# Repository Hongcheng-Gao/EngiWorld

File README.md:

[English](README.md) | [简体中文](README_CN.md)

<h1 align="center">EngiWorld</h1>
<p align="center"><strong>What Can Frontier Agents Deliver in Professional Engineering Environments?</strong></p>

<p align="center">
  <a href="https://engiworld.github.io/">🌐 Website</a> ·
  <a href="https://arxiv.org/abs/2609.37686">📄 Paper</a> ·
  <a href="task/">🧩 Tasks &amp; Verifiers</a> ·
  <a href="https://huggingface.co/datasets/HongchengGao/EngiWorld-Tasks">🤗 Task Dataset</a> ·
  <a href="https://huggingface.co/datasets/HongchengGao/EngiWorld-Images">🤗 Environment Images</a>
</p>

<p align="center"></p>

<p align="center"></p>

<p align="center"><em>Six task types for engineering software use and artifact-based evaluation. Click to enlarge.</em></p>

EngiWorld evaluates whether agents can operate professional engineering software and deliver the requested engineering artifacts. This repository provides all **1,301 tasks**, their evaluators, and the GUI/CLI evaluation runtime. The paper uses a 306-task main-experiment subset, listed in [`task/splits/main-306.txt`](task/splits/main-306.txt).

The full set of 1,301 tasks and their verifiers is also available in the [Hugging Face task dataset](https://huggingface.co/datasets/HongchengGao/EngiWorld-Tasks), with a [dataset viewer](https://huggingface.co/datasets/HongchengGao/EngiWorld-Tasks/viewer/default/tasks) for browsing task instructions and metadata.

The benchmark covers CAD, CAE, CAM, BIM, EDA, and DCC. Its six task types are Single-Software Execution (931), Software Selection (140), Vision-Guided Modeling (120), Design Optimization (40), Cross-Software Coordination (60), and Open-Environment Engineering (10).

Local evaluation launches Windows or Ubuntu virtual machines through Docker on Linux, calls the model, and saves evaluation results.

## ☁️ Run on Alibaba Cloud or Volcengine

Use the [cloud evaluation guide](runtime/deploy/cloud/README.md) for single-task or
Redis-scheduled batch evaluation on either cloud. Explicit model presets, API
interruption handling and batch state management are shared. Images require
compatible engineering applications and desktop services.

## 💾 Installation

Prepare an x86_64 Linux server with Python 3.10, [Docker Engine](https://docs.docker.com/engine/install/), and `zstd`. With `/dev/kvm`, the VM uses hardware acceleration. Without it, the Docker runner attempts software emulation, which starts and runs more slowly. Each environment defaults to 4 CPUs and 16 GB RAM.

Get the code and enter the runtime directory:

```bash
git clone --branch main --single-branch --depth 1 https://github.com/Hongcheng-Gao/Engiworld.git &&
cd Engiworld/runtime
```

Install the runtime in a Python `venv` environment:

```bash
python3.10 -m venv .venv
source .venv/bin/activate
python -m pip install -e ".[worker-api,download]"
```

Run the following commands from `runtime/`.

## 💾 Download complete data before evaluation

The complete dataset provides all **1,301 task definitions, drawings, evaluators, and required ground-truth files**. GitHub includes every drawing and evaluator plus smaller task resources. Download the complete data before starting evaluation.

| Source | Complete task data | Environment images |
|---|---|---|
| Hugging Face | [EngiWorld-Tasks](https://huggingface.co/datasets/HongchengGao/EngiWorld-Tasks) | [EngiWorld-Images](https://huggingface.co/datasets/HongchengGao/EngiWorld-Images) |
| ModelScope | [EngiWorld-Tasks](https://modelscope.cn/datasets/HongchengGao/EngiWorld-Tasks) | [EngiWorld-Images](https://modelscope.cn/datasets/HongchengGao/EngiWorld-Images) |

Use `--source modelscope` in the commands below to download from ModelScope.

**Hugging Face:**

```bash
python -m engiworld.prepare_tasks --source hf --task-root ../data/task
python -m engiworld.prepare_images --source hf --image LibreCAD2.2.0.2 --image-root ../environment-images
```

**ModelScope:**

```bash
python -m engiworld.prepare_tasks --source modelscope --task-root ../data/task
python -m engiworld.prepare_images --source modelscope --image LibreCAD2.2.0.2 --image-root ../environment-images
```

```bash
zstd -d ../environment-images/images/LibreCAD2.2.0.2.qcow2.zst
docker pull happysixd/osworld-docker
python -m engiworld.prepare_tasks --task-root ../data/task --check
```

Downloads verify checksums and preserve modified local files. ModelScope image downloads use 8 parallel range streams by default; set `MODELSCOPE_DOWNLOAD_PARALLEL_WORKERS` to adjust this. Omitting --image downloads all 15 public archives (about 98 GB compressed). Choose the image matching the task snapshot from manifest.json. Snapshots outside the public catalog require a matching image prepared by the user. Decompress the selected archive and prepare the Docker runner before evaluation. Task preparation uses the published dataset directly.

## 🚀 Start from local data

The following commands read already downloaded task data and the local image.

### 1. Start a task

```bash
python -m engiworld.local_eval \
  --task-root ../data/task \
  --task single-software-execution/gui/librecad/task-08 \
  --image ../environment-images/images/LibreCAD2.2.0.2.qcow2 \
  --smoke-test
```

This starts the VM, loads the task inputs, and saves a `smoke.png` screenshot in the results directory without calling a model.

**Servers without KVM:** Check whether the server provides `/dev/kvm`:

```bash
test -e /dev/kvm && echo "KVM available" || echo "Software emulation"
```

If the output says `Software emulation`, run the same `--smoke-test` command above. The runtime selects software emulation automatically; no arguments need to change. Startup may take several minutes. When the terminal shows `"status": "environment_ready"` and `smoke.png` appears in the results directory, open the screenshot to confirm that LibreCAD and the input drawing are ready. Then follow step 2 to run and score a model.

### 2. Run a model and score the task

Configure an OpenAI-compatible Chat Completions endpoint and run the task:

```bash
export OPENAI_BASE_URL="https://your-api-endpoint/v1"
export OPENAI_API_KEY="your-api-key"

python -m engiworld.local_eval \
  --task-root ../data/task \
  --task single-software-execution/gui/librecad/task-08 \
  --image ../environment-images/images/LibreCAD2.2.0.2.qcow2 \
  --model your-model-name \
  --result-dir results
```

When the run finishes, summary.json summarizes the run, result.txt holds the score, and traj.jsonl records model actions. For another task, change --task and use its matching local image. Complete-data preparation already supplies its resources. See the [runtime guide](runtime/README.md) for more options.

## Repository layout

```text
task/<category>/<gui|cli>/<software or software1--software2>/<task-number>/
runtime/
```

Task categories are `single-software-execution`, `cross-software-coordination`, `software-selection`,
`design-optimization`, `vision-guided-modeling`, and `open-environment-engineering`.
Open-Environment Engineering tasks use **CLI** in a blank environment and live under
`task/open-environment-engineering/cli/agent-selected/`; the agent chooses and installs its tools.

Task JSON IDs follow `<category>--<gui|cli>--<software>--<task-number>--<os>`, for example
`single-software-execution--gui--librecad--task-08--ubuntu`. Use either this ID or its task
directory path with `--task`. See the [task guide](task/README.md).

Directory categories and JSON IDs follow the updated paper taxonomy as of 2026-10-09. `task/aliases.json` preserves historical JSON IDs and directory names; the runtime continues to accept them for task selection. See the full [ID migration map](task/id-migration-20261009.json) and [task taxonomy](task/taxonomy.json).

## 📊 Evaluation results

The main experiment evaluates seven models on the same **306 tasks**: **158 CLI** and **148 GUI**, including all 10 Open-Environment Engineering tasks. EngiScore is the mean task score on a 0–100 scale. Execution metrics average all 306 tasks, including unsuccessful runs; output tokens are reported per turn, in thousands.

| Model | EngiScore | CLI | GUI | Turns/task | Tokens (K/turn) | Cost ($/task) |
| --- | ---: | ---: | ---: | ---: | ---: | ---: |
| Claude Opus 5 | **44.7** | 48.6 | 40.5 | 69.5 | 2.4 | 18.78 |
| GPT-5.6 Sol | 38.6 | 47.9 | 28.6 | 54.2 | 1.0 | 9.57 |
| Qwen3.8 Max | 26.3 | 35.3 | 16.6 | 107.3 | 2.7 | 6.44 |
| Gemini 3.7 Flash | 26.1 | 37.2 | 14.2 | 110.0 | 0.7 | 2.08 |
| DeepSeek V4.1 Flash | 25.9 | 48.3 | 2.0 | 115.3 | 9.8 | 0.80 |
| Kimi K3 | 24.3 | 31.3 | 16.7 | 92.1 | 0.9 | 5.85 |
| Qwen3.8 Flash | 16.7 | 31.5 | 1.0 | 119.6 | 1.3 | 0.44 |

## 📚 Citation

If you use EngiWorld in your research, please cite:

```bibtex
@misc{engiworld2026,
  title = {EngiWorld: What Can Frontier Agents Deliver in Professional Engineering Environments?},
  author = {Hongcheng Gao and Hailong Qu and Yu Lei and Henghui Sun and Haoyang Li and Yipeng Wei and Naihao Xue and Xiaohan Yu and Zhuo Tao and Yihe Zang and Yajiao Wang and Jingyi Tang and Yi Li and Jingjing Zhou and Jie Luo and Bohan Zeng and Chengyu Shen and Hao Jiang and Chong Chen and Bowen Qu and Olive Huang and Zeqiang Wang},
  year = {2026},
  eprint = {2609.37686},
  archivePrefix = {arXiv},
  primaryClass = {cs.AI},
  url = {https://arxiv.org/abs/2609.37686}
}
```

## 📄 License

EngiWorld's original code is released under the [MIT License](LICENSE). See [Third-party notices](THIRD_PARTY_NOTICES.md) for component licenses.

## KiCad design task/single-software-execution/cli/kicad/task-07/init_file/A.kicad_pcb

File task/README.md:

[English](README.md) | [简体中文](README_CN.md)

# EngiWorld tasks

The 1,301 tasks use a common directory layout:

```text
<category>/<gui|cli>/<software or software1--software2>/<task-number>/
```

| Directory category | Paper task type | Full tasks |
|---|---|---:|
| `single-software-execution` | Single-Software Execution | 931 |
| `software-selection` | Software Selection | 140 |
| `vision-guided-modeling` | Vision-Guided Modeling | 120 |
| `design-optimization` | Design Optimization | 40 |
| `cross-software-coordination` | Cross-Software Coordination | 60 |
| `open-environment-engineering` | Open-Environment Engineering | 10 |

Software names are lowercase, without version numbers. Multiple names are joined
with `--`. Open-Environment Engineering tasks use `cli/agent-selected/`. Interface folders contain
only the modes available in that category.

Each task contains a `task-*.json` definition, `init_file/` inputs, and its evaluator
(`eval.py`, with `ground_truth/` where required). IDs use
`<category>--<gui|cli>--<software>--<task-number>--<os>`; operating systems retain
`ubuntu` or `windows` from the task. Reverse-modeling tasks retain a `-reverse`
suffix on the task number to distinguish them from same-numbered tasks.

From `../runtime/`, run `python -m engiworld.prepare_tasks --source hf --task-root ../data/task` to download task resources.
Use either a task directory or its JSON ID with `python -m engiworld.local_eval --task-root ../data/task --task`.
Follow the [quick start](../README.md) to run an evaluation.

The paper's 306-task main-experiment subset is listed in [`splits/main-306.txt`](splits/main-306.txt). The scheduler accepts it through `--task-id-file ../task/splits/main-306.txt`.

Directory categories and JSON IDs follow the updated paper taxonomy as of 2026-10-09. `task/aliases.json` preserves historical JSON IDs and directory names; the runtime continues to accept them for task selection. See the full [ID migration map](id-migration-20261009.json) and [task taxonomy](taxonomy.json).

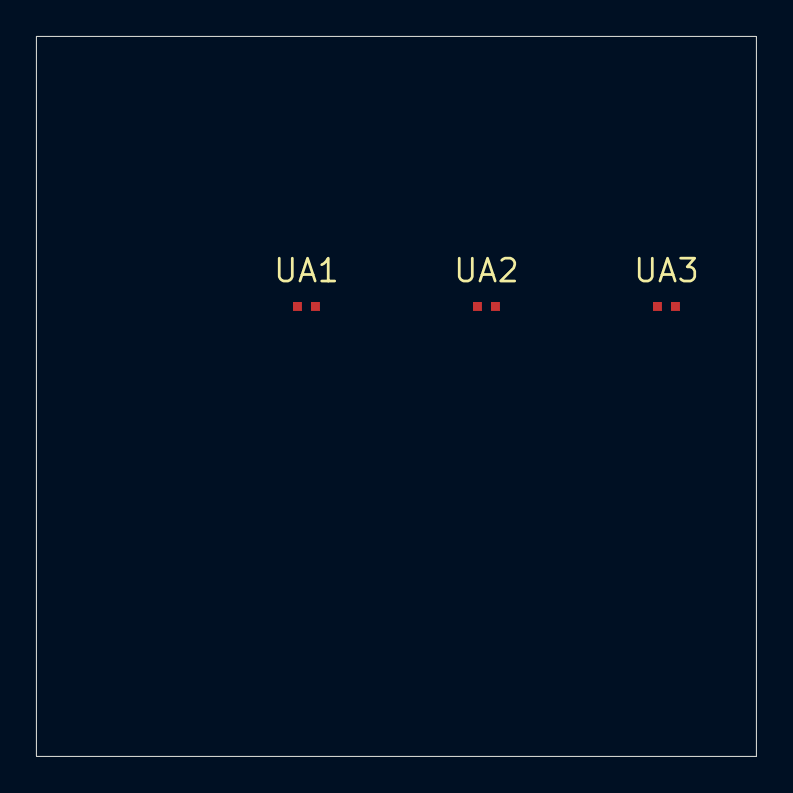
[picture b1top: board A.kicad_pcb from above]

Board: 2 copper layers, 40.0 x 40.0 mm, 3 parts (0 on the bottom side), 2 nets, no tracks yet.

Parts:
UA1: 10k; R_0402_1005Metric
UA2: 22k; R_0402_1005Metric
UA3: 100nF; C_0402_1005Metric

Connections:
GND: UA1.2, UA2.2, UA3.2
VCC: UA1.1, UA2.1, UA3.1

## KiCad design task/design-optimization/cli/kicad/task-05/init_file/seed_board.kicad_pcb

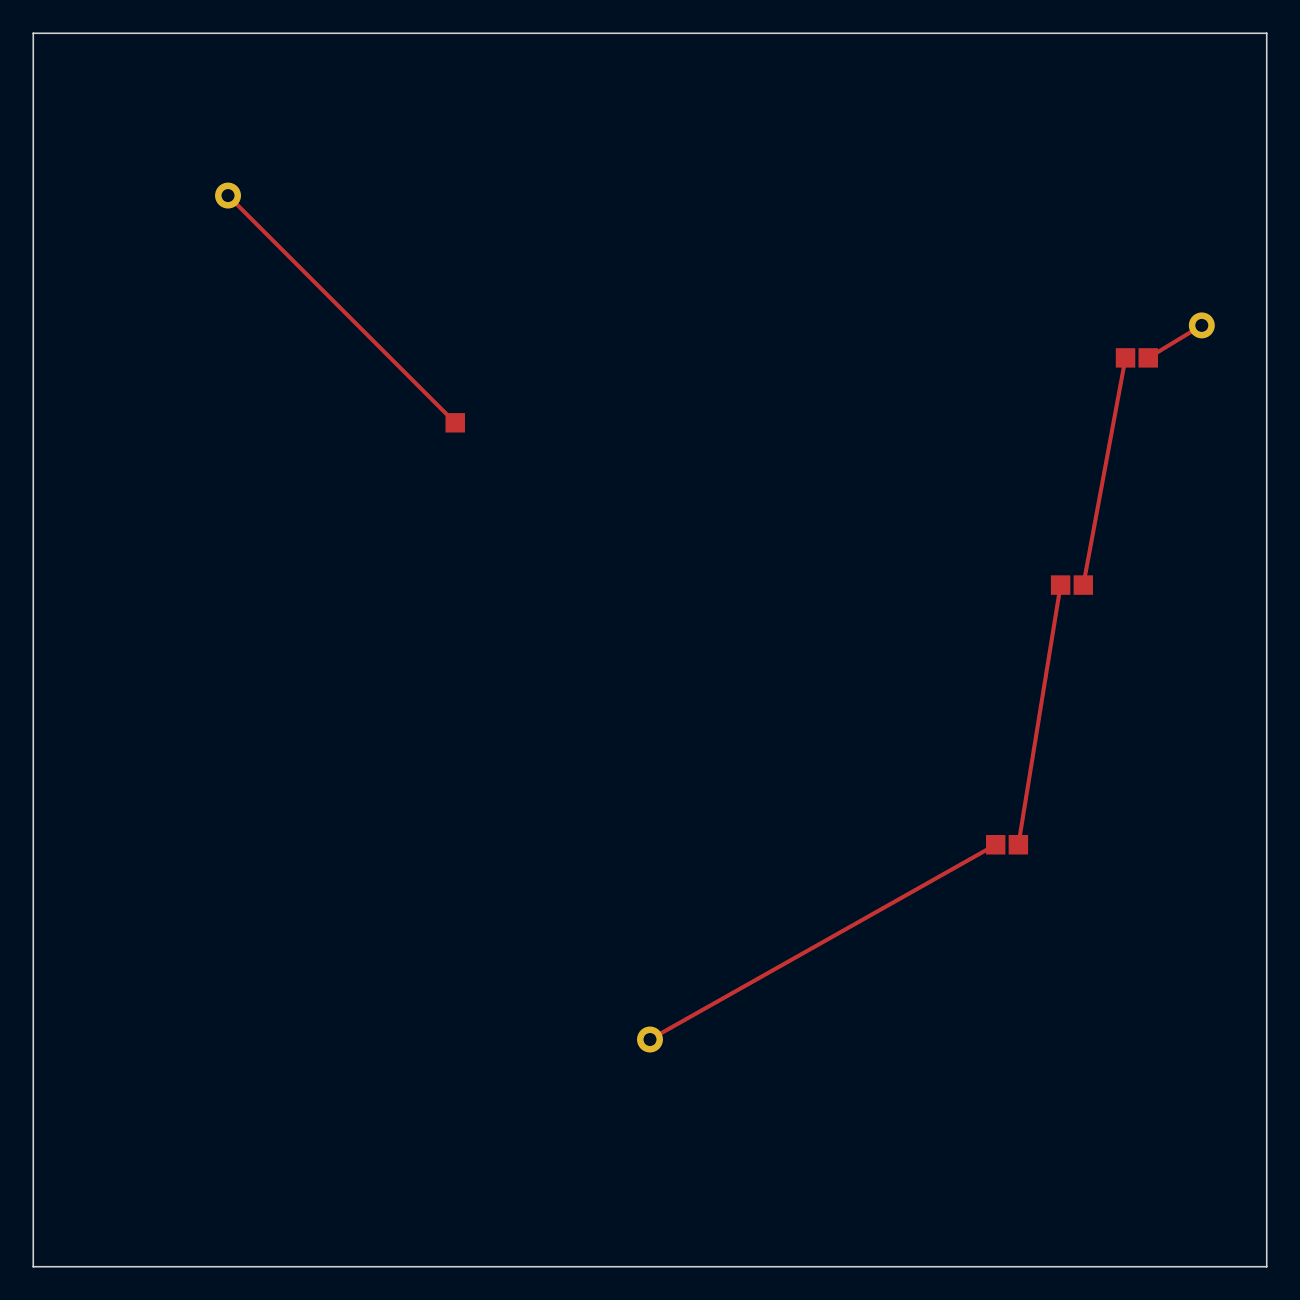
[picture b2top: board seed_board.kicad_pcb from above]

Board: 2 copper layers, 76.0 x 76.0 mm, 7 parts (0 on the bottom side), 5 nets.

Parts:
A1: A1
C1: C1
C2: C2
J1: J1
L1: L1
TP1: TP1
U1: U1

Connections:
A1_C1: A1.1, C1.1
C1_C2: C1.2, C2.1
C2_L1: C2.2, L1.1
L1_J1: J1.1, L1.2
U1_TP1: TP1.1, U1.1

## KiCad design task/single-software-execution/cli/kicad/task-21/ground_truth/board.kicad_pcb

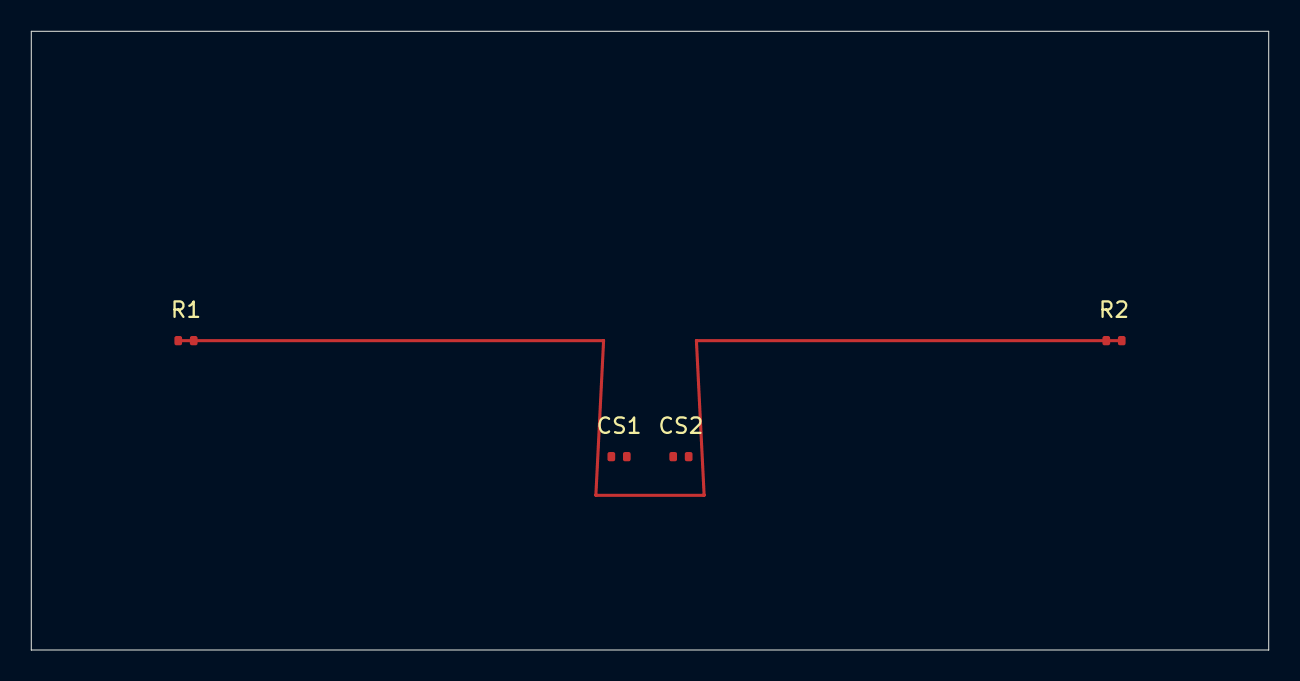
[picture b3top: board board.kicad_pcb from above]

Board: 4 copper layers, 80.0 x 40.0 mm, 4 parts (0 on the bottom side), 3 nets.

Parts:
CS1, CS2: 100n; C_0402
R1, R2: 100; R_0402

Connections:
+3V3: CS1.2, CS2.2
GND: CS1.1, CS2.1
HS1: R1.1, R1.2, R2.1, R2.2

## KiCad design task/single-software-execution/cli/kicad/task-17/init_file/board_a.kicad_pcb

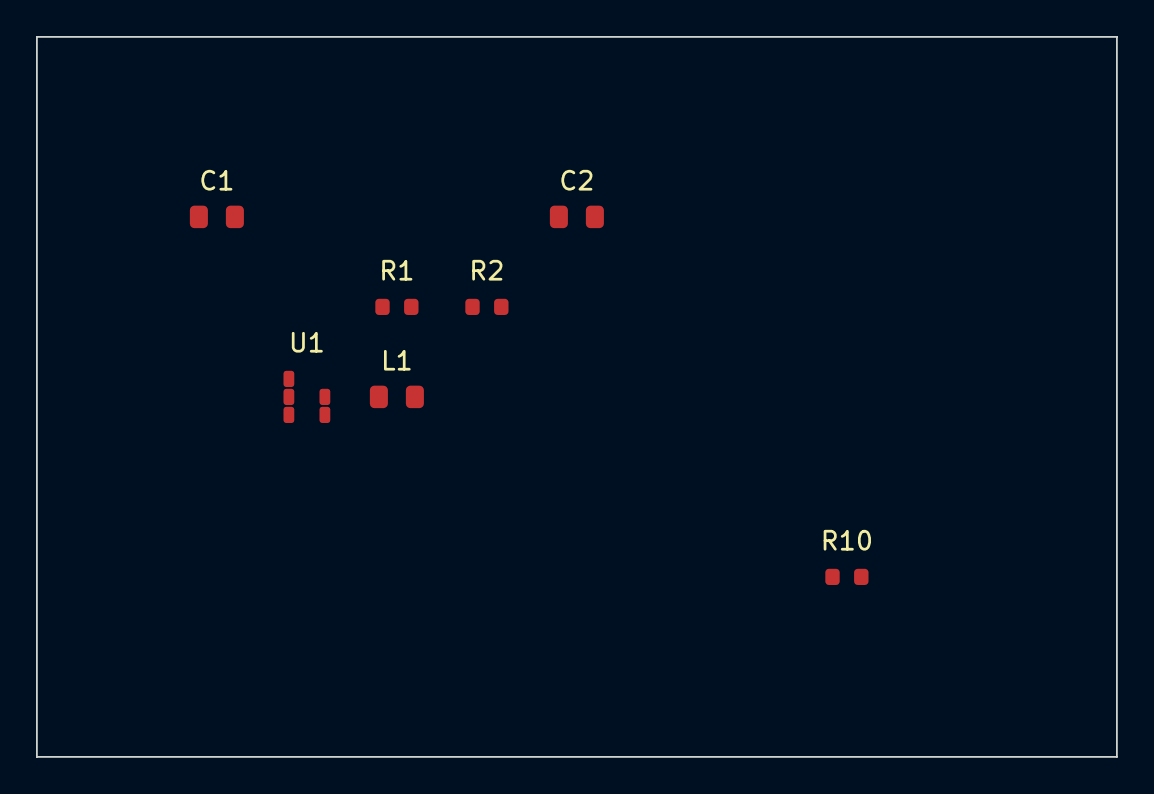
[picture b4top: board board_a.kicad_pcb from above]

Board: 2 copper layers, 60.0 x 40.0 mm, 7 parts (0 on the bottom side), 5 nets, no tracks yet.

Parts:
C1: 10uF; C_0805
C2: 22uF; C_0805
L1: 4u7; L_0805
R1: 10k; R_0603
R2: 2k2; R_0603
R10: 1k; R_0603
U1: LM3671; SOT-23-5

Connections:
FB: R1.2, R2.1, U1.4
GND: C1.2, C2.2, R2.2, R10.2, U1.2
SW: L1.1, U1.1
VIN: C1.1, U1.3, U1.5
VOUT: C2.1, L1.2, R1.1, R10.1

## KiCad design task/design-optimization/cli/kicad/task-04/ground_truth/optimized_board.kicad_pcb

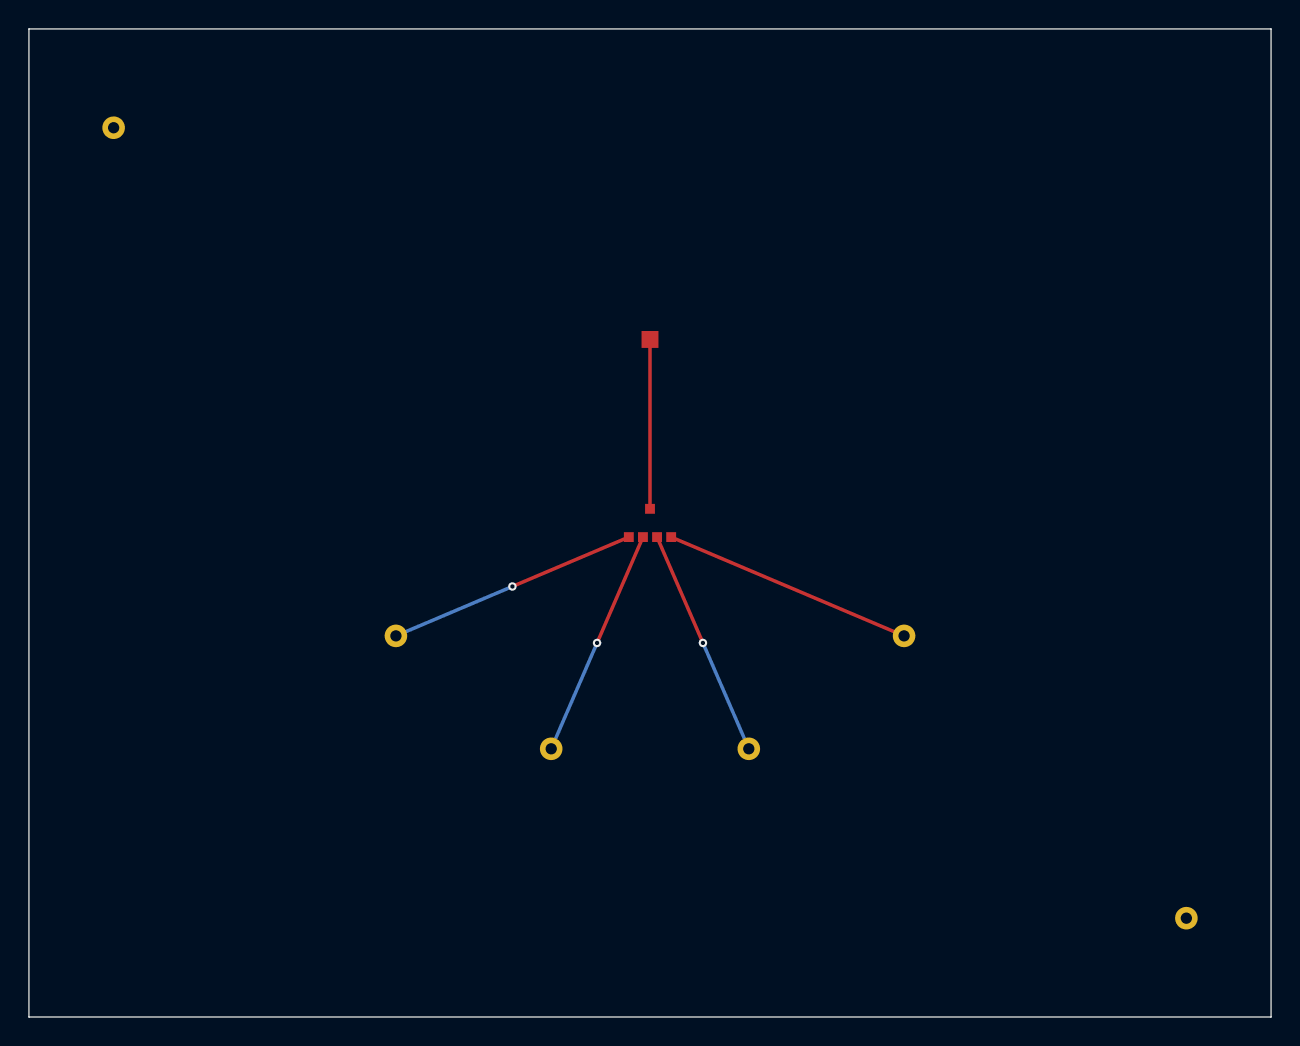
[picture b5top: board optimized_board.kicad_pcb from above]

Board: 2 copper layers, 88.0 x 70.0 mm, 8 parts (0 on the bottom side), 5 nets.

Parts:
C1: C1
J1: J1
J2: J2
TP1, TP2, TP3, TP4: POGO_TEST
U1: U1

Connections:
C1_U1: C1.1, U1.5
TP1_U1: TP1.1, U1.1
TP2_U1: TP2.1, U1.2
TP3_U1: TP3.1, U1.3
TP4_U1: TP4.1, U1.4

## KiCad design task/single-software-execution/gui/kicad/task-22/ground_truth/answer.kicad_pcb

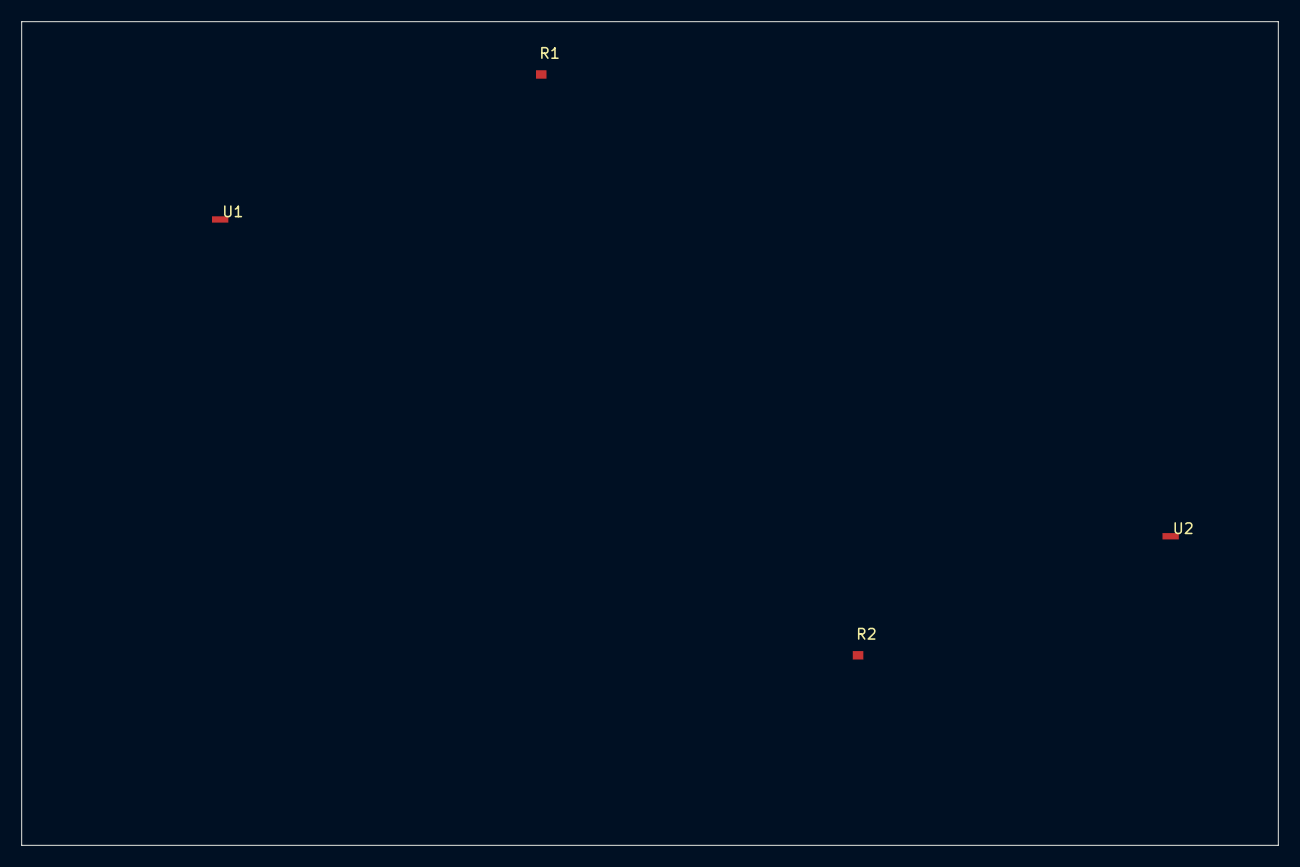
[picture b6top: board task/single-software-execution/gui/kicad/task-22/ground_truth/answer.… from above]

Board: 2 copper layers, 119.0 x 78.0 mm, 4 parts (0 on the bottom side), 2 nets, no tracks yet.

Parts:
R1: 4.7k; R_0603_1608Metric
R2: 10k; R_0603_1608Metric
U1: OPAMP; SOIC-8_3.9x4.9mm_P1.27mm
U2: ADC; SOIC-8_3.9x4.9mm_P1.27mm

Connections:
GND: R2.1, U2.1
VCC: R1.1, U1.1

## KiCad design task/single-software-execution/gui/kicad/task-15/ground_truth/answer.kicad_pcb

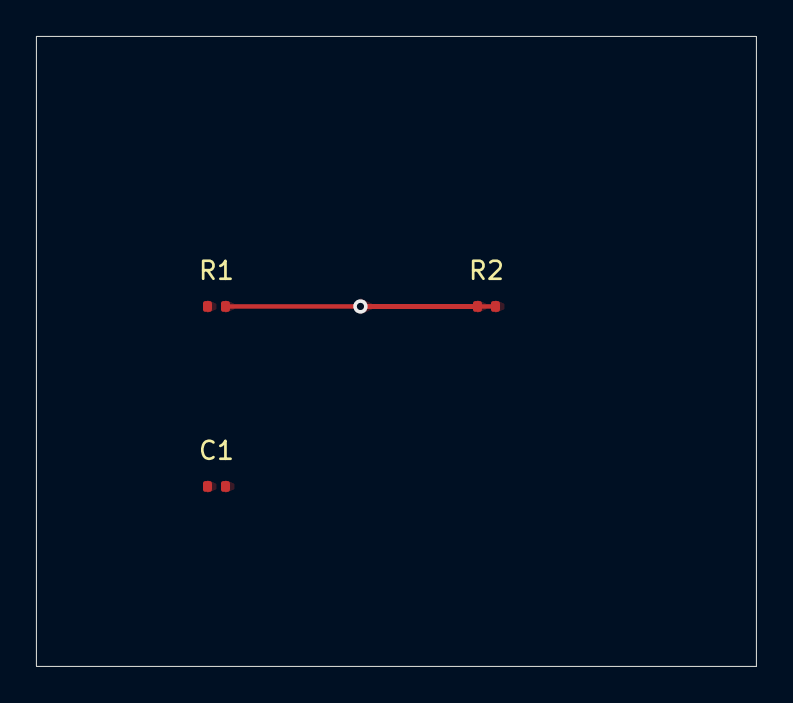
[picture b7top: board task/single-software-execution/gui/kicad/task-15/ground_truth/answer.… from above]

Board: 2 copper layers, 40.0 x 35.0 mm, 3 parts (0 on the bottom side), 2 nets.

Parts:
C1: 100n; C_0402
R1, R2: 10k; R_0402

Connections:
GND: C1.2, R2.2
SIG_A: R1.1, R1.2, R2.1

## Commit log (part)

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2026-05-01 Add task and task-gt directories
    Standalone branch containing only task/ and task-gt/ datasets.
    Made-with: Cursor
2026-05-01 删除多余的e
    1
2026-05-01 修改反斜杠问题+utf-8问题+launch命令不匹配问题
2026-05-01 删除gt
2026-05-01 Replace blender task-11 with machining task
2026-05-01 新增case
2026-05-01 删掉多余的脚本
2026-05-01 改数据的bug
2026-05-01 add enter for launch
2026-05-01 add click for launch
2026-05-01 modified px to ratio for precision
2026-05-01 add GUI operation for eagle
2026-05-02 调整kicad命令
2026-05-02 删去多余文件
2026-05-02 修改ansys路径
2026-05-02 改open到look
2026-05-02 修改eagle的初始化，删去多余的case
2026-05-02 加入task-gt
2026-05-02 对齐id规范
2026-05-02 修改id
2026-05-03 替换yihe的数据
2026-05-03 修复gt
2026-05-03 加入检测软件的脚本
2026-05-03 修数据bug。反斜杠问题
2026-05-03 add test
2026-05-03 add GUI tests
2026-05-03 修改软件镜像和启动和改了revit的启动文件的命令
2026-05-03 clean temp files and update task assets
2026-05-03 update abaqus and ansys
2026-05-04 fix brlcad
2026-05-04 fix autocad -c 20 task check_and_eval.py
2026-05-04 fix brlcad -c check_and_eval.py check_software()
2026-05-04 复制task-gt到task以及更新true到True
2026-05-04 加brlcad的镜像名
2026-05-04 修改brlcad的json
2026-05-04 修改true大小写问题
2026-05-04 fix brlcad empty launch problem
2026-05-05 fix brlcad instruction eval.py consistency problem
2026-05-05 fix D:\Engiworld\task\task-v\librecad instruction absolute path and the consistency of eval and instruction
2026-05-05 删除有问题的task以及部分无法安装环境的task
2026-05-05 fix solvespace eval instruction unconsisitency
2026-05-05 add check.md
2026-05-06 删去instruction里的gui和cli说明
2026-05-06 fix autocad brlcad openscad eval instruction unconsistency
2026-05-07 abaqus
2026-05-08 增加freecad cli数据难度，已经验证eval和instruction一致性
2026-05-13 fix solidcam solidworks nx-cam
2026-05-13 fix solidcam nxcam bug
2026-05-14 CAE修改
2026-05-16 Add Blender and Cadence OrCAD tasks
2026-05-16 Convert Blender tasks to Ubuntu
2026-05-16 修改-c数据里的id里的-v的错误以及删除openfast对应的不用os的数据
2026-05-16 Add Blender and SketchUp task-c sets
2026-05-16 fix lacking windows 后缀
2026-05-16 数据优化
2026-05-16 修改launch以及对应的instruction
2026-05-17 修改revit的launch，增加无法完成的task
2026-05-17 Normalize engineering task metadata and evaluators
2026-05-17 bim tasks refinement: 修改了instruction
2026-05-17 Improve PDF parsing fallback and ignore DS_Store
2026-05-17 bim task refinement
2026-05-17 修改cad cam instruction初始文件描述
2026-05-17 修复eval.py输出和json 里的expected匹配的问题
2026-05-17 fix一部分的cli task中初始文件含有json的情况的任务
2026-05-17 Refine engineering task metadata and instructions
2026-05-17 Update SketchUp portable paths
2026-05-17 openfoam格式修改
2026-05-17 14. 之前扣掉了一些task后，不要出现缺号，保证编号连续，16. instruction统一成一大段的形式，18. 把\r\n统一改成\n，给每个task-c的task加一下instruction最后的prompt。根据osworld改不可完成的任务
2026-05-17 -v instruction增加强制使用GUI的说明
2026-05-18 修改python到python3
2026-05-18 fix librecad python3
2026-05-18 fix freecad
2026-05-18 Fix Blender and KiCad Ubuntu GT checks
2026-05-19 Tighten GUI-only validation for BIM tasks
2026-05-19 Fix GUI task startup configs
2026-05-19 Rename FreeCAD path ground truth outputs
2026-05-19 windows修改
2026-05-19 修改user
2026-05-19 Fix Blender and OrCAD GT evaluation
2026-05-20 Use task-specific AutoCAD seed filenames
2026-05-20 Rename SolidCAM GT outputs to match evaluators
2026-05-20 Rename NX CAM GT outputs to match evaluators
2026-05-20 加上快捷方式
2026-05-20 删除了sketchup和nx-camwq
2026-05-20 check数据，修改没更新的aba和ansys的路径
2026-05-20 增加eval的check py等脚本非法的方式
2026-05-20 Stabilize SOLIDWORKS CAM v tasks
2026-05-20 修改GUI检测
2026-05-20 补全修改GUI检测
2026-05-20 清理不要的文件
2026-05-20 Update AD and ZBrush snapshots
2026-05-20 Align AutoCAD instructions with evaluators
2026-05-20 Fix SolveSpace DXF import workflow
2026-05-20 评测数据
2026-05-21 插入solid的两个软件插入回车
2026-05-21 Flatten openstudio eplusout sql outputs
2026-05-21 ansys修改
2026-05-21 给每个-v都增加py脚本检测，以及增加instruction不能用py的描述
2026-05-21 Add simple GUI task suites
2026-05-21 Stop tracking DS_Store files
2026-05-21 Stabilize KiCad and ZBrush GUI setup
2026-05-22 Update Archicad task windows for GUI import
2026-05-22 Refine Revit GUI IFC tasks
2026-05-22 Increase CAD benchmark difficulty and coverage
    Adds hard task suites and updates supporting CAD task assets/evaluators so benchmark coverage better exercises multi-step geometry, GUI workflows, and deterministic validation.
    Constraint: User requested committing all current workspace modifications before pushing.
    Rejected: Splitting only the FreeCAD hard tasks | current request explicitly asked for all current modifications.
    Confidence: medium
    Scope-risk: broad
    Directive: Keep instruction text deterministic and avoid evaluator logic that depends on hidden ground-truth oracle files.
2026-05-22 Prevent SolveSpace GUI-only task bypass by direct DXF authoring
    Keep task-03 assessing interactive SolveSpace work instead of accepting pyautogui-plus-DXF-dump shortcuts. The evaluator now catches direct authoring traces and generated-DXF signatures while preserv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
    Constraint: GUI-only SolveSpace task must reject direct file authoring without breaking the valid geometry check.
    Rejected: Relying only on final DXF geometry | allowed token GUI actions followed by direct DXF writes.
    Confidence: high
    Scope-risk: narrow
    Directive: Keep task/task-v and task-last/task-v SolveSpace task-03 mirrors synchronized.
2026-05-22 Rewrite OpenStudio task sets
2026-05-22 Rewrite Bonsai GUI tasks
2026-05-23 Increase Eagle GUI task difficulty
2026-05-23 Fix Eagle GUI task feasibility
2026-05-28 eval修改
2026-06-01 Update task-v GUI task assets
2026-06-01 Add task-v GUI test reports
2026-06-02 Add Archicad simple GUI test reports
2026-06-02 Refine Revit simple GUI tasks
2026-06-02 Update openstudio_simple GUI tests
2026-06-02 Clarify SolidWorks GUI task instructions
2026-06-03 Refine simple task benchmarks
2026-06-04 Refine AutoCAD GUI task instructions and evaluators
2026-06-04 Update AutoCAD hard array instructions
2026-06-04 Update OpenSCAD task-v expert revisions
2026-06-04 Refine SolidCAM task instructions and evaluators
2026-06-05 Add AutoCAD final benchmark tasks
2026-06-05 Add final LibreCAD GUI evaluation tasks
2026-06-05 Add OpenSCAD final benchmark tasks
2026-06-07 Refine SolveSpace task difficulty and evaluators
2026-06-07 Harden AutoCAD CLI tasks
2026-06-07 Update FreeCAD CLI task instructions
2026-06-07 Align SolidCAM CLI tasks
2026-06-07 Clarify SolidWorks CLI task instructions
2026-06-07 Align FreeCAD Path CLI tasks
2026-06-07 Clarify OpenSCAD task-c instructions
2026-06-07 Clarify FreeCAD task instructions
2026-06-08 Refine OpenStudio task suite
2026-06-08 Update bonsai task suite
2026-06-08 Refine Archicad CLI tasks
2026-06-08 Rebuild Revit CLI benchmark tasks
2026-06-08 Fix BRL-CAD task-c evaluators
2026-06-08 CAE
    CAE更新
2026-06-09 zbrush startup
2026-06-10 Create final task selection
2026-06-11 Remove Blender generated answer scripts
2026-06-11 Update ANSYS snapshot name
2026-06-11 Remove unsupported task-c setup timeouts
2026-06-11 Flatten Blender ground truth outputs
2026-06-11 Add task-false and remove Revit final tasks
2026-06-30 Sync harder Blender Eagle KiCad tasks to final
